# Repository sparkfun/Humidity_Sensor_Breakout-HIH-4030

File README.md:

SparkFun Humidity Sensor Breakout - HIH-4030
========================================

[*SparkFun Humidity Sensor Breakout - HIH-4030 (SEN-09569)*](https://www.sparkfun.com/products/9569)

This is a breakout board for Honeywell’s HIH-4030 humidity sensor. 
The HIH-4030 measures relative humidity (%RH) and delivers it as an analog output voltage. 

Repository Contents
-------------------

* **/Hardware** - Eagle design files (.brd, .sch)
* **/Production** - Production panel files (.brd)

Documentation
--------------
* **[SparkFun Fritzing repo](https://github.com/sparkfun/Fritzing_Parts)** - Fritzing diagrams for SparkFun products.
* **[SparkFun 3D Model repo](https://github.com/sparkfun/3D_Models)** - 3D models of SparkFun products. 

License Information
-------------------
This product is _**open source**_! 

The **hardware** is released under [Creative Commons ShareAlike 4.0 International](https://creativecommons.org/licenses/by-sa/4.0/).

Please use, reuse, and modify these files as you see fit. Please maintain attribution to SparkFun Electronics and release anything derivative under the same license.

Distributed as-is; no warranty is given.

- Your friends at SparkFun.

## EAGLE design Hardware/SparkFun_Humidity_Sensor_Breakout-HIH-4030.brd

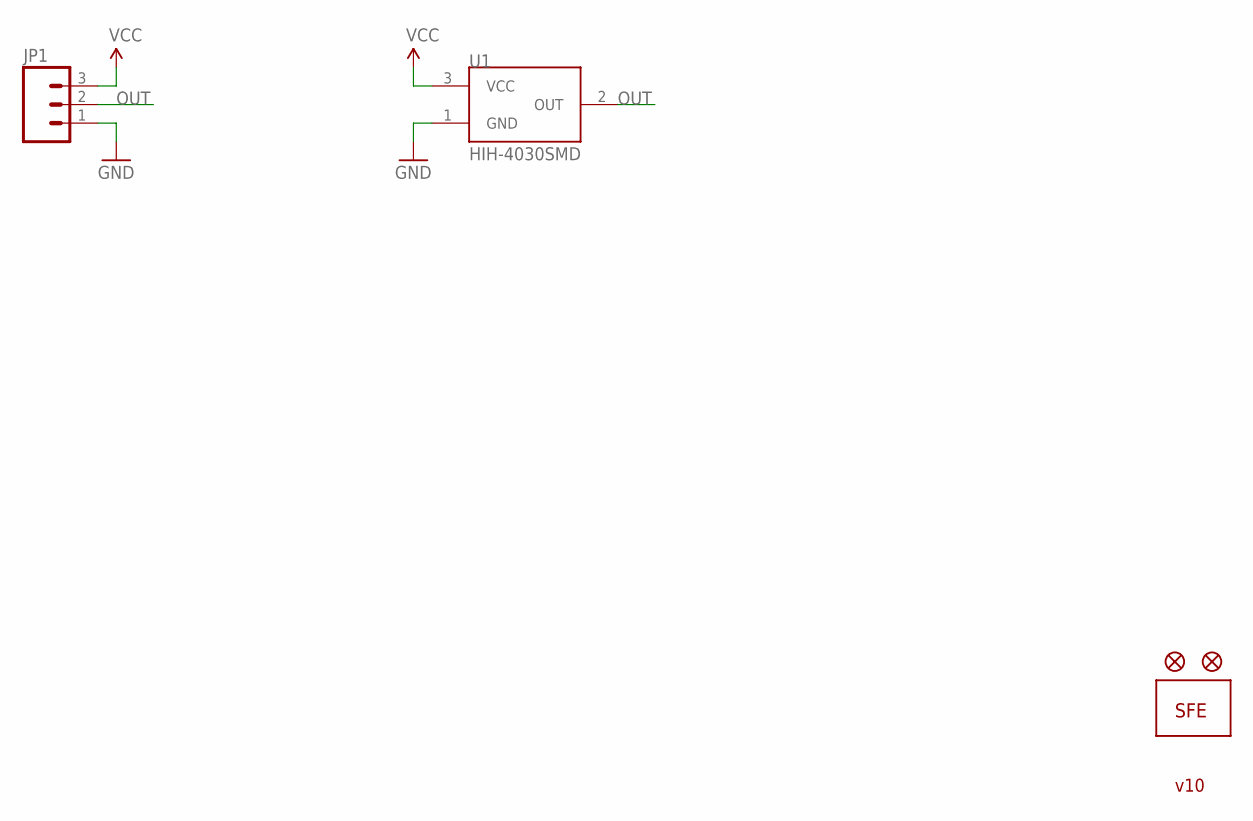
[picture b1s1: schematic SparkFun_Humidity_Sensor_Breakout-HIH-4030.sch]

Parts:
FID1, FID2: FIDUCIALUFIDUCIAL; MICRO-FIDUCIAL
JP1: M03PTH; 1X03
JP2: LOGO-SFESK; SFE-LOGO-FLAME
U1: HIH-4030SMD; HIH-4030

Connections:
GND: JP1.1, U1.1 (GND)
OUT: JP1.2, U1.2 (OUT)
VCC: JP1.3, U1.3 (VCC)

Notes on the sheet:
v10

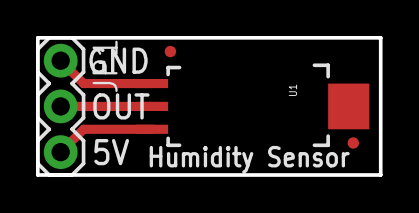
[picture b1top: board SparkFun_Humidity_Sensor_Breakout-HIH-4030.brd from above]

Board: 2 copper layers, 19.1 x 7.6 mm, 5 parts (1 on the bottom side), 3 nets.

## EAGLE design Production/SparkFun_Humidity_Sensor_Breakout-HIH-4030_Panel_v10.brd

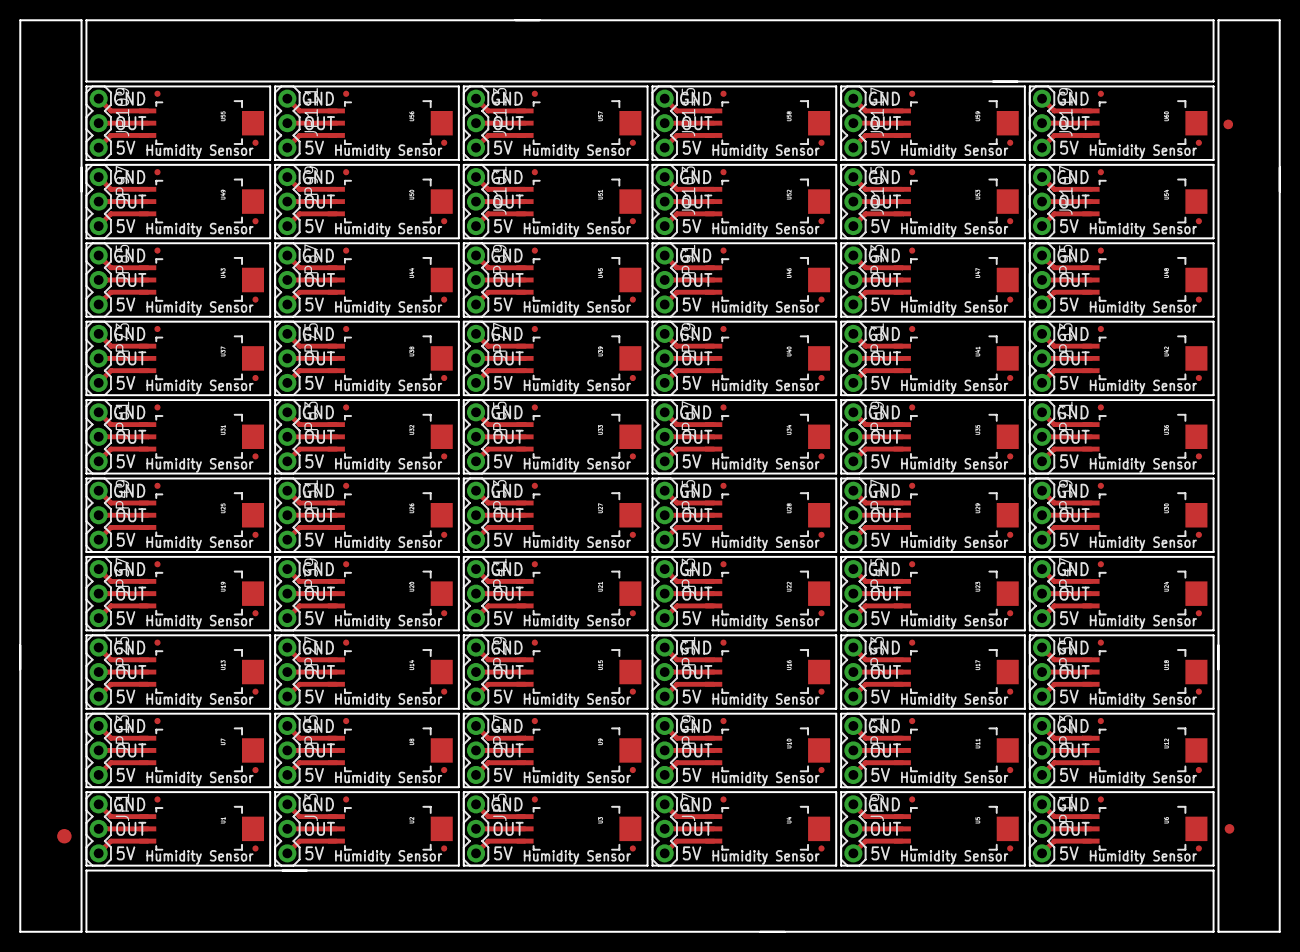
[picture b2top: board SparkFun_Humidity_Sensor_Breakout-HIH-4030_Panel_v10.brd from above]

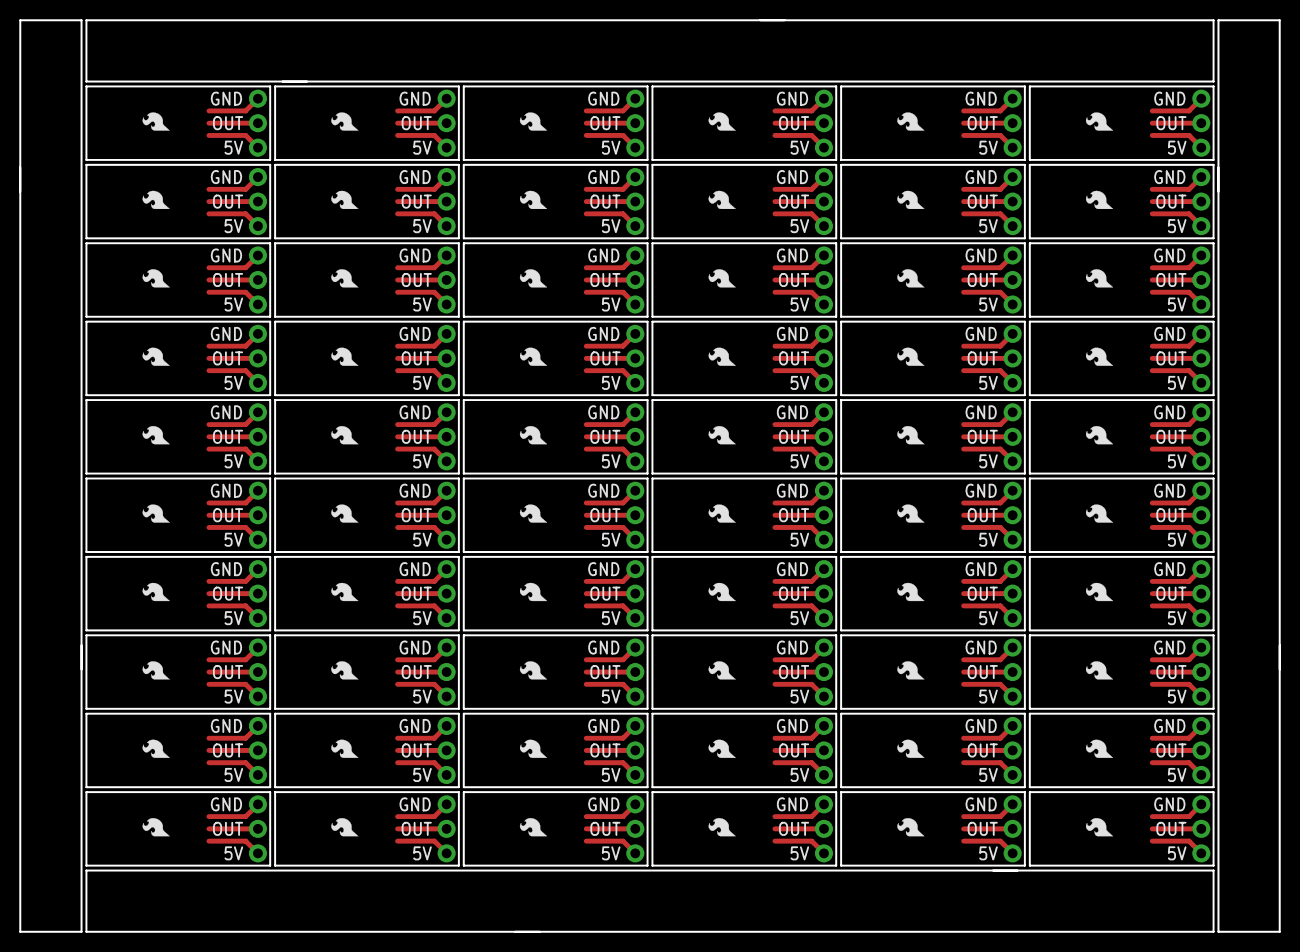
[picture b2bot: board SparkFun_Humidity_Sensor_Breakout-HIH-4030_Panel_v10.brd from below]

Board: 2 copper layers, 130.6 x 94.5 mm, 303 parts (60 on the bottom side), 180 nets.

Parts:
E$1: FIDUCIAL-1.5X3
E$5, E$7: FIDUCIAL-1X2
FID1, FID2, FID3, FID4, FID5, FID6, FID7, FID8, FID9, FID10, FID11, FID12, FID13, FID14, FID15, FID16, FID17, FID18, FID19, FID20, FID21, FID22, FID23, FID24, FID25, FID26, FID27, FID28, FID29, FID30, FID31, FID32, FID33, FID34, FID35, FID36, FID37, FID38, FID39, FID40, FID41, FID42, FID43, FID44, FID45, FID46, FID47, FID48, FID49, FID50, FID51, FID52, FID53, FID54, FID55, FID56, FID57, FID58, FID59, FID60, FID61, FID62, FID63, FID64, FID65, FID66, FID67, FID68, FID69, FID70, FID71, FID72, FID73, FID74, FID75, FID76, FID77, FID78, FID79, FID80, FID81, FID82, FID83, FID84, FID85, FID86, FID87, FID88, FID89, FID90, FID91, FID92, FID93, FID94, FID95, FID96, FID97, FID98, FID99, FID100, FID101, FID102, FID103, FID104, FID105, FID106, FID107, FID108, FID109, FID110, FID111, FID112, FID113, FID114, FID115, FID116, FID117, FID118, FID119, FID120: FIDUCIALUFIDUCIAL; MICRO-FIDUCIAL
JP1, JP3, JP5, JP7, JP9, JP11, JP13, JP15, JP17, JP19, JP21, JP23, JP25, JP27, JP29, JP31, JP33, JP35, JP37, JP39, JP41, JP43, JP45, JP47, JP49, JP51, JP53, JP55, JP57, JP59, JP61, JP63, JP65, JP67, JP69, JP71, JP73, JP75, JP77, JP79, JP81, JP83, JP85, JP87, JP89, JP91, JP93, JP95, JP97, JP99, JP101, JP103, JP105, JP107, JP109, JP111, JP113, JP115, JP117, JP119: 1X03
JP2, JP4, JP6, JP8, JP10, JP12, JP14, JP16, JP18, JP20, JP22, JP24, JP26, JP28, JP30, JP32, JP34, JP36, JP38, JP40, JP42, JP44, JP46, JP48, JP50, JP52, JP54, JP56, JP58, JP60, JP62, JP64, JP66, JP68, JP70, JP72, JP74, JP76, JP78, JP80, JP82, JP84, JP86, JP88, JP90, JP92, JP94, JP96, JP98, JP100, JP102, JP104, JP106, JP108, JP110, JP112, JP114, JP116, JP118, JP120: LOGO-SFESK; SFE-LOGO-FLAME
U1, U2, U3, U4, U5, U6, U7, U8, U9, U10, U11, U12, U13, U14, U15, U16, U17, U18, U19, U20, U21, U22, U23, U24, U25, U26, U27, U28, U29, U30, U31, U32, U33, U34, U35, U36, U37, U38, U39, U40, U41, U42, U43, U44, U45, U46, U47, U48, U49, U50, U51, U52, U53, U54, U55, U56, U57, U58, U59, U60: HIH-4030SMD; HIH-4030

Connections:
GND: JP1.1, U1.1
GND1: JP3.1, U2.1
GND2: JP5.1, U3.1
GND3: JP7.1, U4.1
GND4: JP9.1, U5.1
GND5: JP11.1, U6.1
GND6: JP13.1, U7.1
GND7: JP15.1, U8.1
GND8: JP17.1, U9.1
GND9: JP19.1, U10.1
GND10: JP21.1, U11.1
GND11: JP23.1, U12.1
GND12: JP25.1, U13.1
GND13: JP27.1, U14.1
GND14: JP29.1, U15.1
GND15: JP31.1, U16.1
GND16: JP33.1, U17.1
GND17: JP35.1, U18.1
GND18: JP37.1, U19.1
GND19: JP39.1, U20.1
GND20: JP41.1, U21.1
GND21: JP43.1, U22.1
GND22: JP45.1, U23.1
GND23: JP47.1, U24.1
GND24: JP49.1, U25.1
GND25: JP51.1, U26.1
GND26: JP53.1, U27.1
GND27: JP55.1, U28.1
GND28: JP57.1, U29.1
GND29: JP59.1, U30.1
GND30: JP61.1, U31.1
GND31: JP63.1, U32.1
GND32: JP65.1, U33.1
GND33: JP67.1, U34.1
GND34: JP69.1, U35.1
GND35: JP71.1, U36.1
GND36: JP73.1, U37.1
GND37: JP75.1, U38.1
GND38: JP77.1, U39.1
GND39: JP79.1, U40.1
GND40: JP81.1, U41.1
GND41: JP83.1, U42.1
GND42: JP85.1, U43.1
GND43: JP87.1, U44.1
GND44: JP89.1, U45.1
GND45: JP91.1, U46.1
GND46: JP93.1, U47.1
GND47: JP95.1, U48.1
GND48: JP97.1, U49.1
GND49: JP99.1, U50.1
GND50: JP101.1, U51.1
GND51: JP103.1, U52.1
GND52: JP105.1, U53.1
GND53: JP107.1, U54.1
GND54: JP109.1, U55.1
GND55: JP111.1, U56.1
GND56: JP113.1, U57.1
GND57: JP115.1, U58.1
GND58: JP117.1, U59.1
GND59: JP119.1, U60.1
OUT: JP1.2, U1.2
OUT1: JP3.2, U2.2
OUT2: JP5.2, U3.2
OUT3: JP7.2, U4.2
OUT4: JP9.2, U5.2
OUT5: JP11.2, U6.2
OUT6: JP13.2, U7.2
OUT7: JP15.2, U8.2
OUT8: JP17.2, U9.2
OUT9: JP19.2, U10.2
OUT10: JP21.2, U11.2
OUT11: JP23.2, U12.2
OUT12: JP25.2, U13.2
OUT13: JP27.2, U14.2
OUT14: JP29.2, U15.2
OUT15: JP31.2, U16.2
OUT16: JP33.2, U17.2
OUT17: JP35.2, U18.2
OUT18: JP37.2, U19.2
OUT19: JP39.2, U20.2
OUT20: JP41.2, U21.2
OUT21: JP43.2, U22.2
OUT22: JP45.2, U23.2
OUT23: JP47.2, U24.2
OUT24: JP49.2, U25.2
OUT25: JP51.2, U26.2
OUT26: JP53.2, U27.2
OUT27: JP55.2, U28.2
OUT28: JP57.2, U29.2
OUT29: JP59.2, U30.2
OUT30: JP61.2, U31.2
OUT31: JP63.2, U32.2
OUT32: JP65.2, U33.2
OUT33: JP67.2, U34.2
OUT34: JP69.2, U35.2
OUT35: JP71.2, U36.2
OUT36: JP73.2, U37.2
OUT37: JP75.2, U38.2
OUT38: JP77.2, U39.2
OUT39: JP79.2, U40.2
OUT40: JP81.2, U41.2
OUT41: JP83.2, U42.2
OUT42: JP85.2, U43.2
OUT43: JP87.2, U44.2
OUT44: JP89.2, U45.2
OUT45: JP91.2, U46.2
OUT46: JP93.2, U47.2
OUT47: JP95.2, U48.2
OUT48: JP97.2, U49.2
OUT49: JP99.2, U50.2
OUT50: JP101.2, U51.2
OUT51: JP103.2, U52.2
OUT52: JP105.2, U53.2
OUT53: JP107.2, U54.2
OUT54: JP109.2, U55.2
OUT55: JP111.2, U56.2
OUT56: JP113.2, U57.2
OUT57: JP115.2, U58.2
OUT58: JP117.2, U59.2
OUT59: JP119.2, U60.2
VCC: JP1.3, U1.3
VCC1: JP3.3, U2.3
VCC2: JP5.3, U3.3
VCC3: JP7.3, U4.3
VCC4: JP9.3, U5.3
VCC5: JP11.3, U6.3
VCC6: JP13.3, U7.3
VCC7: JP15.3, U8.3
VCC8: JP17.3, U9.3
VCC9: JP19.3, U10.3
VCC10: JP21.3, U11.3
VCC11: JP23.3, U12.3
VCC12: JP25.3, U13.3
VCC13: JP27.3, U14.3
VCC14: JP29.3, U15.3
VCC15: JP31.3, U16.3
VCC16: JP33.3, U17.3
VCC17: JP35.3, U18.3
VCC18: JP37.3, U19.3
VCC19: JP39.3, U20.3
VCC20: JP41.3, U21.3
VCC21: JP43.3, U22.3
VCC22: JP45.3, U23.3
VCC23: JP47.3, U24.3
VCC24: JP49.3, U25.3
VCC25: JP51.3, U26.3
VCC26: JP53.3, U27.3
VCC27: JP55.3, U28.3
VCC28: JP57.3, U29.3
VCC29: JP59.3, U30.3
VCC30: JP61.3, U31.3
VCC31: JP63.3, U32.3
VCC32: JP65.3, U33.3
VCC33: JP67.3, U34.3
VCC34: JP69.3, U35.3
VCC35: JP71.3, U36.3
VCC36: JP73.3, U37.3
VCC37: JP75.3, U38.3
VCC38: JP77.3, U39.3
VCC39: JP79.3, U40.3
VCC40: JP81.3, U41.3
VCC41: JP83.3, U42.3
VCC42: JP85.3, U43.3
VCC43: JP87.3, U44.3
VCC44: JP89.3, U45.3
VCC45: JP91.3, U46.3
VCC46: JP93.3, U47.3
VCC47: JP95.3, U48.3
VCC48: JP97.3, U49.3
VCC49: JP99.3, U50.3
VCC50: JP101.3, U51.3
VCC51: JP103.3, U52.3
VCC52: JP105.3, U53.3
VCC53: JP107.3, U54.3
VCC54: JP109.3, U55.3
VCC55: JP111.3, U56.3
VCC56: JP113.3, U57.3
VCC57: JP115.3, U58.3
VCC58: JP117.3, U59.3
VCC59: JP119.3, U60.3

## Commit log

2015-05-05 Adding hardware files, updating README
2015-10-19 added local fiducials
2015-10-19 created panel v10

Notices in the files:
parts and their libraries:
SparkFun-Aesthetics: Licensing: Creative Commons ShareAlike 4.0 International - https://creativecommons.org/licenses/by-sa/4.0
